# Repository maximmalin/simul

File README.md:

# FULLY AUTOMATED HARDWARE DEVELOPMENT PIPELINE.

lAST TESTED PROJECT IS DEVELOPMENT OF 2 WATT LED DRIVER 
---

**Start here**

* [`AGENT_MAP.md`](AGENT_MAP.md) — comprehensive functional map of the project (architecture, subsystems, data flow, entry points, how to run/verify).
* [`sim/COSIM_STATUS.md`](sim/COSIM_STATUS.md) — co-simulation status: what is verified, what is blocked, and why.
* [`manifest.json`](manifest.json) — machine-readable project description, generated by `python3 tools/dump_manifest.py`.
* [`technical_task_en.md`](technical_task_en.md) / [`technical_task.md`](technical_task.md) — the technical task (EN / RU).
* [`LICENSE`](LICENSE) — MIT.

---

## 1. What it is

| | |
|---|---|
| **Product** | Zero-IF (direct-conversion) SDR receiver |
| **MCU** | STM32F103C8T6 Blue Pill (Cortex-M3) |
| **Frequency range** | 0.5 – 30 MHz |
| **Architecture** | Direct conversion, quadrature I/Q, USB I/Q to host |
| **Circuit source of truth** | SKiDL (`sim/scripts/sdr_skidl_circuit.py`) — 60 parts, 38 nets |
| **Analog simulator** | ngspice 44.2 |
| **Digital/co-sim** | FMI 2.0 (`pythonfmu` / `fmpy`), QEMU (`qemu-system-arm`), PicSimLab |
| **PCB / 3D** | KiCad 9, tscircuit, FreeCAD, Elmer FEM, openEMS FDTD, NEC-2 |
| **License** | MIT |

The MCU is **never "inside" ngspice**. The analog/digital boundary is explicit at
the STM32 pins, and that contract (PA0/PA1 = ADC I/Q, PA6 = LO, PA7 = GAIN) is
asserted both by the firmware and by `verify_pin_contract.py`.

---

## 2. The spine — signal/flow of truth

```
sim/scripts/sdr_skidl_circuit.py   SKiDL = the single source of truth for connectivity
        │
        ▼
sim/scripts/export_ngspice.py      → sim/netlists/sdr_skidl_ngspice.cir (ngspice deck)
        │
        ▼
sim/scripts/build_fmu.py           → sim/fmu/SdrNgspiceFMU.fmu  (FMI 2.0 slave)
        │
        ▼
sim/scripts/cosim_fmu_stm32.py     hard-lockstep: firmware model  <->  ngspice
sim/scripts/test_fmu_cosim.py      regression through fmpy's FMI master
sim/scripts/cosim_real_stm32.py    the same, but the MCU is the real firmware.elf on QEMU
```

The system in one picture:

```
                        ┌─────────────────────────────────────────────┐
                        │            HOST / OFF-BOARD                  │
  sim/scripts/          │  SKiDL → ngspice deck → FMI FMU              │
  sdr_skidl_circuit.py  │        └── sim/netlists/sdr_skidl_ngspice.cir │
  export_ngspice.py     │                    │                         │
  build_fmu.py          │                    ▼                         │
                        │        sim/fmu/SdrNgspiceFMU.fmu             │
                        │                    │  FMI 2.0 setReal/doStep │
                        └────────────────────┼─────────────────────────┘
                                             │
             ┌───────────────────────────────┼───────────────────────────────┐
             │                               │                               │
    cosim_fmu_stm32.py           cosim_real_stm32.py            sdr_picsimlab_cosim.py
    (firmware MODEL in Python)   (REAL firmware.elf on QEMU)    (PicSimLab rcontrol)
             │                               │                               │
             │                     qemu-system-arm + GDB RSP          PicSimLab NOGUI
             │                     firmware/src/cosim.h mailbox       src/picsimlab_fmu/*
             ▼                               ▼                               ▼
      ┌──────────────────────────────── analog boundary (pins) ──────────────────┐
      │ PA0 = ADC_I   PA1 = ADC_Q   PA6 = LO (TIM3_CH1)   PA7 = GAIN             │
      └──────────────────────────────────────────────────────────────────────────┘
```

Antennas have their own physics path:

```
sim/inputs/antenna_*.yaml → sim/scripts/antenna_fdtd.py → S11/Zin
                          → sim/scripts/export_antenna_ngspice.py → Touchstone (ngspice)
```

---

## 3. Functionality index

Every piece of functionality in the repository, grouped by subsystem.

### 3.1 Circuit source of truth — SKiDL
* **`sim/scripts/sdr_skidl_circuit.py`** — the unified SKiDL netlist generator. The
  *only* place connectivity is defined: 60 parts, 38 nets. Writes the KiCad
  schematic and the netlist consumed downstream. Never hand-edit generated
  netlists; change this file and regenerate.

### 3.2 Analog netlist & ngspice
* **`sim/scripts/export_ngspice.py`** — emits the behavioral zero-IF receiver
  chain to `sim/netlists/sdr_skidl_ngspice.cir`:
  * LNA stages as transconductance macromodels (not ideal VCVS),
  * quadrature LO derived from a real 90° all-pass (`H = 1 − 2/(1+sRC)`),
  * zero-IF mixer with mid-rail-biased limiting baseband buffers,
  * RF chokes as L+R (the ferrite bead uses its DC resistance),
  * the STM32 pin boundary (see §3.4).
* Other decks: `sim/netlists/sdr_receiver.cir`, `sim/netlists/sdr_simplified.cir`,
  `sim/netlists/bridge_check.cir`.
* XSPICE bridges: analog→digital (`adc_bridge`) with datasheet CMOS thresholds;
  digital→analog modelled explicitly as a host-alterable source behind the pin's
  output resistance and load capacitance (an ngspice `dac_bridge` input cannot be
  driven from outside ngspice).

### 3.3 Direct-conversion physics (verified)
* LO is a **real 7.2 MHz timer waveform**; the beat lands at **48.1 kHz** with a
  50 kHz IF offset.
* I/Q amplitude ratio **0.965**, phase **+91.6°**.
* The **Q channel is driven by a real 90° all-pass on the LO**, not wired to zero.
* Five original analog defects (dead Q, DC LO, 0 V-centred ADC, DC-biased LNA gain,
  bare-resistor chokes) were found and fixed; the fix log lives in
  `sim/COSIM_STATUS.md`.
* Two measurement traps (ngspice `print` 80-column truncation and non-uniform
  adaptive timesteps) are documented there too.

### 3.4 STM32 pin model — datasheet-derived boundary
| Parameter | Value | Source |
|---|---|---|
| Output impedance | 65 Ω | DS5319 Table 30, I<sub>IO</sub> = 20 mA |
| Pin capacitance C<sub>IO</sub> | 5 pF | DS5319 Table 29 |
| Input low V<sub>IL</sub> | 0.35·V<sub>DD</sub> = 1.155 V | DS5319 Table 29 |
| Input high V<sub>IH</sub> | 0.65·V<sub>DD</sub> = 2.145 V | DS5319 Table 29 |
| Input leakage | 1 µA | DS5319 Table 29 |

Numbers are taken from the datasheet, not chosen for convenience.

### 3.5 Verification suite
| Script | What it proves |
|---|---|
| `sim/scripts/test_sdr_netlist.py` | 22 regression checks on the SKiDL→ngspice export |
| `sim/scripts/verify_pin_contract.py` | 31 closed-loop analog + pin-contract checks |
| `sim/scripts/test_ngspice_nets.py` | Smoke tests for the ngspice decks |
| `sim/scripts/test_fmu_cosim.py` | Drives the FMU through fmpy's FMI master, checks the pin boundary |
| `tests/requirements/**` | Requirement-matrix tests (RF, antenna, AO, system) |
| `tests/stress/test_co_simulation.py` | Bragg FMU + ngspice antenna 2-port stress test |

### 3.6 FMI 2.0 co-simulation (the FMU)
* **`sim/scripts/sdr_ngspice_fmu.py`** — a self-contained FMI 2.0 co-simulation
  slave bundling an embedded ngspice deck (self-contained on purpose: `pythonfmu`
  bundles only this one file).
* **`sim/scripts/build_fmu.py`** — regenerates the netlist from SKiDL and splices
  it into the FMU source, so the FMU and the deck are the same circuit *by
  construction*.
* **`sim/fmu/SdrNgspiceFMU.fmu`** — the built slave.
* **`sim/scripts/cosim_fmu_stm32.py`** — hard-lockstep driver: STM32 firmware
  *model* ↔ ngspice FMU. Real FMI calls (`setReal`/`doStep`/`getReal`) every step;
  pulses cross the boundary at half an LO period; PA6 drives the mixer through the
  65 Ω + 5 pF pin model.
* Build: `<venv>/bin/pythonfmu build -f sim/scripts/sdr_ngspice_fmu.py -d sim/fmu`
  (or `python3 sim/scripts/build_fmu.py`).

### 3.7 Real-firmware co-simulation on QEMU
The actual `firmware.elf` on an emulated Cortex-M, in lockstep with real ngspice.
* **`sim/scripts/cosim_real_stm32.py`** — orchestrator.
* **`sim/scripts/gdb_remote.py`** — a minimal GDB remote-serial-protocol client
  (QEMU's human monitor can read memory with `xp` but has **no write command**;
  the GDB stub can read *and* write *and* single-step).
* **`firmware/src/cosim.h`** — the RAM **mailbox** both sides agree on (magic,
  `host_lo`/`host_gain` in; `mcu_stamp`/`adc_i`/`adc_q`/`adc_stamp` out).
* **`sim/scripts/build_cosim_firmware.py`** — builds the `COSIM_MODE` ELF.
* **`sim/scripts/diag_*.py`** — forensic diagnostics that found the two setup()
  blockers (USB CDC enumeration, PLL wait) and the current stop point.

Status: the core reaches `ADC1_2_IRQHandler`; QEMU's STM32F103 peripheral model
starves `loop()` (an ADC/DMA emulator-fidelity limit). Everything around it —
mailbox, exchange, netlist, FMU — is verified. See `sim/COSIM_STATUS.md`.

### 3.8 PicSimLab bridge package (`src/picsimlab_fmu/`)
* `wrapper.py` — `PicSimLabFMU` co-simulation wrapper (`step()` / `run()`).
* `cosim_bridge.py` — TCP rcontrol ↔ ngspice lockstep loop (+ `parse_pinsl`, `MAX_SAMPLES`).
* `ngspice_bridge.py` — prompt-synced ngspice CLI pipe (`-p`) bridge.
* `pin_mapper.py` — board pin allocation (`ARDUINO_UNO`, `STM32_BLUE_PILL`, `ESP32_DEVKITC`).
* `live_scope.py` — live co-sim oscilloscope (POSIX SHM + semaphores + matplotlib).
* `examples/` — small usage examples.

Drivers and probe scripts:
* `sim/scripts/start_picsimlab.py` — launches PicSimLab NOGUI and polls until the
  rcontrol port accepts (the board comes from the `.ini`; there is **no `board`
  command** in rcontrol).
* `sim/scripts/sdr_picsimlab_cosim.py` — the SDR-specific driver.
* `sim/scripts/rcontrol.py`, `rcontrol_analog.py`, `rcontrol_session.py` —
  low-level rcontrol probing / analog pin driving / one-shot evidence session.
* Config: `firmware/picsimlab_sdr.ini`.

Blocked upstream: with the QEMU backend running, rcontrol never binds (0.9.2);
0.9.3 has rcontrol but ships no `libqemu-stm32.so`. Full evidence in
`sim/COSIM_STATUS.md`.

### 3.9 Firmware (`firmware/`)
* **`firmware/src/firmware.ino`** — minimal firmware that reaches `loop()` and
  services the mailbox.
  * Pins: `PA0` = ADC_I, `PA1` = ADC_Q, `PA6` = LO (TIM3_CH1), `PA7` = GAIN.
  * Under `COSIM_MODE`, overrides `SystemClock_Config()` to skip the PLL wait
    (QEMU never sets `PLLRDY`).
* **`firmware/src/cosim.h`** — mailbox layout shared with the co-sim host.
* **`firmware/platformio.ini`** — two environments:
  * `bluepill_f103c8` — the shipped image (USB CDC on);
  * `cosim` — USB compiled out (a bench image and a co-sim image can never be
    confused).
* **`firmware/scripts/hex.py`** — post-build `objcopy` to emit Intel HEX for
  PicSimLab's `loadhex`.

### 3.10 Antenna physics
* **`sim/inputs/antenna_*.yaml`** — one file per antenna; adding an antenna = add
  a YAML file, no code edits. Present: dipole 7 MHz, meander 200 MHz, patch
  2.45 GHz.
* **`sim/scripts/antenna_fdtd.py`** — YAML → S11/Zη → Touchstone. All three
  shipped antennas run the **real openEMS FDTD** solver (`fdtd: true`); setting
  `fdtd: false` falls back to an analytic thin-wire / transmission-line estimate
  (marked `model: analytic` in the JSON).
* **`sim/scripts/mesh.py`** — openEMS mesh sizing with a hard memory budget.
* **`sim/scripts/export_antenna_ngspice.py`** — results → ngspice S-parameter networks.
* **`sim/scripts/antenna_sim.py`**, **`smoke_tutorial.py`** — openEMS workflow and
  tutorial smoke test.
* **`sim/scripts/radiation.py`**, **`sim/nec/**`** — NEC-2 radiation patterns for
  the three channels (`sim/nec/channel_{a,b,c}.nec`, `run_nec.py`).
* **`hardware/antenna/**`** — FreeCAD panel geometry (150 × 150 mm FR-4 0.8 mm):
  * Channel A: meander 200 MHz, Channel B: 2×2 patch @ 2.45 GHz, Channel C: 4×4
    patch @ 5.8 GHz; `geometry/build_antennas_fc.py` rebuilds and exports
    STEP/STL.
* Results (`sim/outputs/*.json`, all `model: fdtd`):
  * dipole 7 MHz — f<sub>res</sub> 6.90 MHz, S11 −15.7 dB, η<sub>rad</sub> 98 %.
  * patch 2.45 GHz — f<sub>res</sub> 2442.5 MHz, S11 ≈ −3.6 dB, η<sub>rad</sub> 30.8 %.
  * meander 200 MHz — no usable match anywhere in 50–800 MHz: S11 ≈ 0 dB and
    Z<sub>in</sub> ≈ 5 − 63j Ω at 50 MHz, with |Re Z| only ≈ 0.6–2 Ω at the in-band
    reactance zeros. The printed meander over its full ground plane is a low-Q,
    low-resistance resonator, so the old analytic −12.0 dB estimate was
    optimistic; the FDTD reports the element as effectively non-radiating
    (η = 0 %, `eta_source: unavailable_no_radiated_power`). A genuine full-wave
    result, not a solver failure.

### 3.11 Web GUI
* **`sim/web_gui/app.py`** — Flask app that runs `SdrNgspiceFMU.fmu` via `fmpy`,
  plots I/Q live, exposes `stim_level` / `lo_frequency`, and exports an
  `sdr_cosim.xcos` diagram for Xcos.
* **`sim/web_gui/templates/index.html`** — Plotly dark dashboard.
* Run: `python3 sim/web_gui/app.py` → http://localhost:5000.

### 3.12 Diagnostics
`sim/scripts/diag_*.py` (`infinite`, `literal`, `mailbox`, `pc`, `regs`, `watch`,
`patch`) are the forensic scripts used to find the QEMU blockers and validate the
patch antenna. Kept as the reproducible evidence trail, not scratch.

### 3.13 Hardware / PCB / 3D toolchain
* **`hardware/tscircuit/build_pcb.mjs`** — the PCB stage. Reads the SKiDL netlist
  (`sim/scripts/sdr_skidl_circuit.py` → `hardware/kicad/sdr_receiver.kicad_sch`),
  places parts, autoroutes with explicit Altium-grade design rules and exports
  `out/`: `board.kicad_pcb`, `board.kicad_sch`, `gerbers.zip`, `board.step`,
  `board.{glb,gltf}`, `board.net`, `board_schematic.pdf`, `circuit.json`.
  Run `node hardware/tscircuit/build_pcb.mjs` (or `make pcb`).
* The earlier `hardware/kicad/build_board.py` (`kinet2pcb` + `kicad-cli`) path is
  superseded by the tscircuit emitter.
* **Reliability** — `sim/octave/reliability_model.m` (Octave) reads datasheet
  parameters from `sim/octave/reliability_parts.tsv` (base FIT, Ea, T_ref/T_use,
  π_Q) and computes system MTBF as parts-count + Arrhenius. Requirement **REQ-REL-01**
  (MTBF ≥ 10 000 ч). Run `make reliability` → `out/reliability.json`;
  tests in `tests/requirements/reliability/`.
* **Thermal** — `sim/scripts/thermal_pcb.py` couples **ngspice** (DC operating
  point → dissipated power) with the **PCB CAD** (`circuit.json` → outline,
  stackup, placement). Two levels: *fast* `T_j = T_a + P·θ_JA` and a *deep* 2D FEM
  of heat conduction/spreading over the board. Run `make thermal` →
  `out/thermal_{fast,fem}.json`; tests in `tests/requirements/thermal/`.
* **Reception distance (link budget)** — `sim/scripts/link_budget.py` computes the
  receiver noise floor (REQ-PERF-02), MDS (REQ-PERF-02) and the Friis range per antenna
  channel (A/B/C). Run `make link-budget` → `out/link_budget.{json,svg}`;
  «дальность приёма» сводится по разделам в `requirements/reception_range.md`
  (и столбец `Reception_Distance_m` в `requirements_matrix.csv`).
* **Direction finding** — `sim/scripts/direction_finding.py` implements a phase
  interferometer (Δφ = 2π·d·sinθ/λ), draws the combined bearing + range diagram,
  and emits a NEC-2 `.nec` that opens in
  [EA1FUO/AntennaSim](https://github.com/EA1FUO/AntennaSim)
  (`--antennasim-url` posts to its `/api/v1/simulate`). Run `make direction` →
  `out/direction_finding.{json,svg}`.
* **EMC** — `tests/requirements/emc/` verifies REQ-EMC-01…04: skin depth and
  shielding effectiveness, immunity to 3 V/m (IEC 61000-4-3 level 2), CISPR 22
  Class B emission, supply filters and enclosure zoning.
* `tools/spec.py`, `tools/blocks.py` — the project spec (6 blocks, 24 parts) used
  by the generators.
* `hardware/pipeline.py` — hardware build-pipeline orchestrator.
* `hardware/kicad/kicad_lib.py` — KiCad symbol / schematic helper;
  `hardware/kicad/generate_schematic.py` — full single-sheet `.kicad_sch`
  generation from code; `test_any_schematic.py` — prove the generator is
  schematic-agnostic; `verify_nets.py` — cross-check the KiCad netlist against the
  generator tables.
* `hardware/tscircuit/build_pcb.mjs` — netlist → TSX, placement, model offsets;
  `build_derived.py` (build local derived tables from the JLCPCB part DB),
  `resolve_parts.py` (part substitution by value/footprint), `step2stl.py`
  (STEP → STL with orientation normalization), `check_models3d.py` (glb vs
  circuit.json), `make_viewer.py` + `site_assets.py` (offline 3D viewer),
  `fetch_vendor_models.mjs` / `fetch_3dmodels*.sh` (vendor 3D models),
  `check_net.py` (verify the viewer makes no external requests).
* Part selection / datasheets: `scripts/download-datasheets.js`,
  `scripts/convert-kicad-to-circuit-json.js`, `scripts/post-build-datasheets.js`,
  `scripts/lib/*`.
* Manufacturing output dir: `out/` (board.kicad_pcb, gerbers, BOM, PnP, GLB, STEP).

### 3.14 Engineering drawings & power budget
* **`gost_pipeline.py`** — STEP → cleaned → GOST drawing.
* **`block0_bus_power_calc.py`** — 5 V bus / buck / LC-filter calculation.
* **`gen_spice_from_kicad.py`** — KiCad `.kicad_sch` → SPICE netlist.
* `picsimlab_rt_wrapper.py` — PicSimLab real-time wrapper (from brig-receiver).

### 3.15 Bragg-cell / AOPP toolbox (transferred from brig-receiver)
The acousto-optic branch is kept as a toolbox, **not** part of the SDR signal path:
* **`sim/scripts/bragg_sim.py`** — Gmsh → Elmer FEM pipeline (`Δn = dn_scale·ε_zz`).
* **`sim/scripts/bragg_fmu.py`**, `test_fmu.py`, `test_antenna_fmu.py`,
  `realtime_loop_fmu.py` — FMI blocks and real-time FMU loop.
* **`sim/scripts/msh_to_elmer.py`** — Gmsh `.msh` → Elmer mesh.
* **`sim/inputs/bragg_inputs.yaml`**, `config/params.yaml` — parameters.
* **`sim/octave/bragg_formulas.m`** + `README_formulas.md` — formulas and an
  analytic self-check (Hooke + photoelasticity).
* **`sim/cad/`** — FreeCAD parametric Bragg-cell scripts: `make_bragg_cell_fc.py`
  (build), `refresh_cad.py` (regenerate), `import_elmer_mesh_fc.py`, `cad_dims.json`.
  No `.FCStd`/`.step` is checked in — they are generated.
* `sim/outputs/elmer_results.json`, `sim/outputs/nec_results.json`, `openems_results.json`.

### 3.16 Requirements, plan, tests & CI
* **Requirements matrix** — `requirements/requirements_matrix.csv` (37 requirements + header) and
  per-subsystem `requirements/*/REQ-*.md`; SNR and noise floor are project-wide
  requirements **REQ-PERF-02** (SNR, noise floor, MDS).
* **Plan** — `plan/plan.md`, `plan/blocks.md`, `plan/README.md`, `plan/checks.py`.
* **Technical task** — `technical_task.md` (RU), `technical_task_en.md` (EN),
  `technical_task_ua.md` (UA), plus per-block TZ in `work/tz-{a..e}/`.
* **Tests** — pytest suites under `tests/requirements/{antenna,rf,ao,system,reliability,thermal}/`,
  `tests/stress/test_co_simulation.py` (co-simulation, needs `fmpy`);
  checklist at `tests/requirements/checklist.csv`.
* **CI** — `.forgejo/workflows/push-{general,fix,feature,docs}.yml` (Elmer-FEM
  physical-constraint jobs on push).
* `references/formulas_and_sources.md`, `issues/` (issue template folder).

### 3.17 Tooling
* **`tools/dump_manifest.py`** — writes `manifest.json`.
* **`tools/init_project.py`** — create a fresh project from tracked files.

---

## 4. Quick start

```bash
cd <repo>

# --- Everything (netlist → PCB → docs → tests → reliability/thermal) ---
make all

# --- Circuit → netlist ---
.venv/bin/python sim/scripts/sdr_skidl_circuit.py     # regenerate SKiDL netlist
.venv/bin/python sim/scripts/export_ngspice.py        # regenerate ngspice deck

# --- Verify (fastest health check) ---
.venv/bin/python sim/scripts/test_sdr_netlist.py      # 22/22 checks
.venv/bin/python sim/scripts/verify_pin_contract.py   # 31/31 checks
.venv/bin/python sim/scripts/test_ngspice_nets.py

# --- FMU co-simulation ---
python3 sim/scripts/build_fmu.py                      # rebuild FMU from SKiDL
.venv/bin/python sim/scripts/cosim_fmu_stm32.py       # lockstep firmware-model ↔ ngspice
.venv/bin/python sim/scripts/test_fmu_cosim.py        # fmpy regression

# --- Real firmware on QEMU ---
.venv/bin/python sim/scripts/build_cosim_firmware.py  # COSIM_MODE ELF
.venv/bin/python sim/scripts/cosim_real_stm32.py      # real firmware ↔ ngspice

# --- PicSimLab ---
.venv/bin/python sim/scripts/start_picsimlab.py       # launch NOGUI, wait for rcontrol
.venv/bin/python sim/scripts/sdr_picsimlab_cosim.py   # drive co-sim

# --- Antennas ---
export LD_LIBRARY_PATH=$HOME/opt/openEMS/lib:$LD_LIBRARY_PATH
<venv-with-openEMS>/bin/python sim/scripts/antenna_fdtd.py sim/inputs/antenna_patch_2450mhz.yaml
.venv/bin/python sim/scripts/export_antenna_ngspice.py sim/outputs/<result>.json

# --- Firmware build ---
cd firmware && pio run                # shipped image
cd firmware && pio run -e cosim       # USB-less co-sim image
cd firmware && pio run -t hex         # emit Intel HEX

# --- Web GUI ---
python3 sim/web_gui/app.py            # http://localhost:5000

# --- Hardware / manifest ---
node hardware/tscircuit/build_pcb.mjs         # real tscircuit emitter
python3 hardware/tscircuit/build_derived.py   # local part table
python3 hardware/tscircuit/resolve_parts.py   # part substitution
python3 tools/dump_manifest.py                # write manifest.json
node scripts/download-datasheets.js           # fetch MPN datasheets
python3 gost_pipeline.py                       # STEP → cleaned → GOST drawing

# --- Reliability / thermal ---
make reliability                              # Octave parts-count MTBF (REQ-REL-01)
make thermal                                  # fast θ_JA + 2D FEM (PCB CAD + ngspice)

# --- Reception distance / direction finding / EMC ---
make link-budget                              # Friis + шум → out/link_budget.{json,svg}
make direction                                # пеленгация (NEC-2 / AntennaSim)
pytest tests/requirements/emc tests/requirements/reception -q
```

> `.venv/bin/python` is the project venv (`skidl`, `pythonfmu`, `fmpy`, `numpy`,
> `matplotlib`). Pure-stdlib tools run fine under system `python3`; the web GUI
> uses `flask` (system `python3`), and antenna FDTD needs a separate
> openEMS-enabled interpreter.

---

## 5. Repository layout

Roles: **source** = keep and edit; **derived** = regenerated by scripts; **data** =
external/binary.

| Path | Role | What it is |
|---|---|---|
| `sim/scripts/` | source | All physics, netlist, co-sim, antenna, diagnostic scripts |
| `sim/netlists/` | derived | ngspice decks (`.cir`) produced by `export_ngspice.py` |
| `sim/inputs/` | source | YAML parameter files (one per antenna) |
| `sim/outputs/` | derived | Physics result JSON/PNG |
| `sim/fmu/` | data | Built FMUs (`SdrNgspiceFMU.fmu`, antenna/Bragg blocks) |
| `sim/work/` | derived | Solver scratch (openEMS, Elmer, gmsh) |
| `sim/web_gui/` | source | Flask I/Q web GUI for the FMU |
| `firmware/` | source | STM32 Arduino sketch, cosim mailbox, PlatformIO config |
| `firmware/src/` | source | `firmware.ino`, `cosim.h` |
| `src/picsimlab_fmu/` | source | PicSimLab rcontrol ↔ ngspice bridge package |
| `hardware/` | source | KiCad generation, PCB/3D pipeline, antenna geometry, FEM |
| `hardware/kicad/` | source | Schematic generator + KiCad symbol/S-expression library |
| `hardware/tscircuit/` | source | PCB emitter, 3D model resolution, part selection, viewer |
| `tools/` | source | Spec (`spec.py`, `blocks.py`), manifest/init tooling |
| `tests/` | source | Requirement-matrix + stress tests |
| `requirements/`, `plan/`, `work/`, `tz/`, `references/`, `config/`, `issues/` | source | Requirements, plan, TZ, formulas, parameters |
| `local_footprints/` | external | Опциональный клон [KiCad/kicad-footprints](https://github.com/KiCad/kicad-footprints) для ручной правки плат в KiCad. Не входит в репозиторий и не нужен для сборки: плату генерирует tscircuit, футпринты берутся из resolved-таблицы деталей. |
| `out/` | derived | Generated board artifacts (gerbers/BOM/GLB/STEP) |
| `node_modules/`, `.venv/` | derived | Dependency installs |
| `.forgejo/` | source | CI workflow definitions |
| `scripts/` | source | Node datasheet/part-selection helpers |

---

## 6. Environment

**System tools:** `python3` (3.13), `ngspice` (44.2), `kicad-cli` (9.0.2),
`node`/`npm` (22 / 10), `pio` (PlatformIO 6.2), `qemu-system-arm` (10.0),
`gdb-multiarch` (16.3), `gmsh` (4.13), Elmer FEM (26.2), openEMS, NEC-2
(`nec2c`), FreeCAD.

**Python venv (`.venv`):** `skidl` 2.3.0, `pythonfmu` 0.7.0, `fmpy` 0.3.32,
`numpy` 2.5.3, `matplotlib`. `flask` is *not* installed here — the web GUI runs
under system `python3` (flask 3.1); `pytest` is installed separately for the
`tests/` suites. Antenna FDTD needs a *separate* openEMS-enabled interpreter.

**External data / installs:**
* `/usr/share/kicad/{symbols,footprints}`
* `$HOME/opt/openEMS` — openEMS install (used via `LD_LIBRARY_PATH`)
* `/mnt/ext4data/jlcparts` — JLCPCB parts DB used by the part resolver
* Elmer / gmsh for the FEM path

**PicSimLab:** NOGUI AppImages in `/mnt/ext4data/downloads/`
(`PICSimLab_NOGUI-0.9.2` has the STM32 backend; `0.9.3` has a working rcontrol but
ships no `libqemu-stm32.so`). See `sim/COSIM_STATUS.md`.

---

## 7. Verified status

| Stage | Evidence |
|---|---|
| SKiDL netlist | 60 parts, 38 nets, KiCad schematic written |
| ngspice deck | `sim/netlists/sdr_skidl_ngspice.cir`, 0 warnings / 0 errors |
| Direct conversion | LO is a real 7.2 MHz timer waveform; beat lands at 48.1 kHz (IF offset 50 kHz); I/Q ratio 0.965; phase +91.6° |
| Q channel | driven by a real 90° all-pass on the LO, not wired to zero |
| STM32 pin model | 65 Ω @ 20 mA; C<sub>io</sub> 5 pF; V<sub>IL</sub>/V<sub>IH</sub> 0.35/0.65·V<sub>DD</sub> |
| Regression tests | `test_sdr_netlist.py` — 22/22 |
| Analog + pin contract | `verify_pin_contract.py` — 31/31 |
| Firmware | cosim build artifacts present (`firmware/.pio/build/cosim/`): `firmware.elf` ≈ 23 KB, `firmware.bin` ≈ 4.6 KB; `.hex` via `pio run -t hex` |
| Antennas | all real openEMS FDTD (`model: fdtd`): dipole 6.90 MHz / S11 −15.7 dB / η<sub>rad</sub> 98 %; patch 2442.5 MHz / −3.6 dB / 31 %; meander reactive with no in-band match (S11 ≈ 0 dB, η<sub>rad</sub> 0 %) — `sim/outputs/*.json` |
| PicSimLab NOGUI rcontrol | answers `version`, `pinsl`, `sim`, `loadhex` |
| STM32 backend | `qemu-stm32 -M stm32-f103c8-picsimlab-new`, 48 pins |

---

## 8. Known limitations / open items

1. **QEMU real-firmware path** stops at `ADC1_2_IRQHandler` — QEMU's STM32F103
   ADC/DMA model is not faithful enough for `loop()` to be serviced. Emulator
   fidelity limit, not a project defect.
2. **PicSimLab rcontrol never binds while QEMU runs** (0.9.2), and **0.9.3 has no
   STM32 backend**. Needs an upstream fix / a 0.9.3-built `libqemu-stm32.so`.
3. **`out/` artifacts are text templates**, not manufacturing outputs.
4. Several transferred brig scripts assume brig's paths/data (e.g. `config/params.yaml`
   points at `/home/mirrage/brig-receiver/...`); adapt before use. Likewise
   `sim/README.md` is the brig Bragg-cell module README, kept as reference.
6. `docs/` is empty; `AGENT_MAP.md` + `sim/COSIM_STATUS.md` + `manifest.json` are
   the authoritative documentation.
7. **Meander 200 MHz does not match in full-wave simulation.** Modelled over its
   full ground plane (matching `hardware/antenna/geometry/build_antennas_fc.py`)
   it is a low-Q reactive resonator — S11 ≈ 0 dB across 50–800 MHz, no net
   radiation (η = 0 %). The project's own definitions also disagree: the YAML/CAD
   use 3 × 63.5 mm arms (220 mm), while `sim/nec/run_nec.py` uses 3 × 130 mm arms
   (430 mm) and its `GN 1 0 0 0 1.0 0.0` ground card is rejected by nec2c. Treat
   the meander figures as a design warning, not a finished antenna.

---

## 9. Conventions

* **One source of truth per thing.** Connectivity = SKiDL; physics = the
  `sim/scripts/*` entry points; parameters = YAML in `sim/inputs/`.
* **Don't hand-edit derived files** (`sim/netlists/`, `sim/outputs/`, `out/`).
* **Pin boundary is a contract.** PA0/PA1 = ADC I/Q, PA6 = LO, PA7 = GAIN. Asserted
  by `verify_pin_contract.py` and by `firmware.ino`.
* **Datasheet numbers, not convenience.** Pin impedance and thresholds come from
  DS5319.
* **Prove it.** Any claim about the analog chain should be backed by
  `test_sdr_netlist.py` / `verify_pin_contract.py` / `test_fmu_cosim.py`.
* **Regenerate, don't patch.** `build_fmu.py` exists precisely so the FMU can't
  drift from SKiDL.

See [`AGENT_MAP.md`](AGENT_MAP.md) for the deep functional map and
[`sim/COSIM_STATUS.md`](sim/COSIM_STATUS.md) for the co-simulation narrative and
evidence.

## 🤖 Агентно-функциональный граф

Заказ приходит текстом, проходит граф функций-агентов и превращается
в сборку. Движок **не знает про Krystal Radio** — всё, что касается
конкретного изделия, лежит в [`agents.project.yaml`](agents.project.yaml).

```
POST /api/order "посчитай дальность и пеленгацию"
        │
        ▼
   ┌──────────┐  модель получает инструменты и решает:
   │supervisor│  list_targets → submit_plan → run_target → read_artifacts
   └────┬─────┘  (или ask_human, когда нужен человек)
        ▼
   ┌──────┐  выполняет вызовы, возвращает модели результат
   │ tools│
   └──┬───┘
      ├─ нужна помощь ─► await_human ─► interrupt() ─► ответ оператора ─┐
      ├─ есть модель ──► supervisor (цикл: думаю → действую → смотрю)  │
      └─ нет модели ───► plan_rules → execute_rules → review          │
                                                                        │
   ┌────────┐ ◄───────────────────────────────────────────────────────┘
   │ report │  факты из артефактов → структурный отчёт (+ резюме модели)
   └────────┘
```

### Почему LangGraph, а не что-то другое

Проверено по документации LangChain: **LangGraph — это agent runtime,
LangChain — framework, Deep Agents — harness**. Runtime даёт наибольший
контроль над тем, что именно выполняется.

Здесь контроль — главное требование. Модель **выбирает** из объявленных
целей, а **исполняет** система сборки. Harness вроде CrewAI или Deep
Agents даёт ReAct-агента с доступом к файловой системе — то есть
ровно то, чего в инженерном проекте быть не должно: агент с правом
писать что угодно был бы не помощью, а источником порчи.

Что взято из рантайма по-современному:

| Возможность | Как реализовано |
|---|---|
| Вызов инструментов | Типизированные схемы в `backend/agents/tools.py`, ответ приходит разобранным. Прежний разбор JSON регуляркой не нужен |
| Цикл «думаю — действую — смотрю» | Узлы `supervisor` ↔ `tools`, не один план на всё |
| Прерывание человека | `interrupt()` — граф встаёт, состояние сохранено, после ответа продолжается с места остановки |
| Долговременное состояние | `SqliteSaver` в `.run/graph.db`; переживает перезапуск моста |
| Устойчивость к обрыву | Недоступный провайдер уходит в паузу на `KR_LLM_COOLDOWN` секунд, чтобы не ждать таймаут на каждом вызове |

Без `langgraph` движок работает на запасном пути (`run_plain`): те же
узлы, те же проверки — теряются только чекпоинты и прерывание.

### Модели: свободные веса, любой рантайм

`Authorization` не отправляется, если ключа нет — поэтому один и тот же
код работает и с облаком, и с локальным сервером. Локальные серверы
**находятся сами**: опрашиваются типовые порты (`11434`, `8080`,
`1234`, `8000`, `5000`…), так что не важно, запущен Ollama, llama.cpp,
LM Studio или vLLM.

```bash
make llm-check                            # что включено, что отвечает, какие модели есть
KR_LLM_PRESET=hermes make llm-check       # то же для другой открытой модели
KR_LLM_ENABLED=0 make llm-check           # проверить, что будет при выключенной модели
```

| Переменная | Смысл |
|---|---|
| `KR_LLM_ENABLED` | Главный выключатель. `0` — план по правилам, сводки структурные |
| `KR_LLM_PRESET` | `hermes`, `qwen`, `llama`, `gemma`, `mistral` |
| `KR_LLM_PROVIDER` | `ollama`, `llamacpp`, `lmstudio`, `vllm`, `openai`, `deepseek`, `groq`, `custom` |
| `KR_LLM_MODEL` | Модель. Если её нет на сервере — подставится та, что есть |
| `KR_LLM_MODEL_FAST` | Отдельная модель для сводок (обычно локальная и дешёвая) |
| `KR_LLM_FALLBACK` | `auto` — откат на живой локальный сервер, либо имя провайдера |

Роли разделены намеренно: планирование требует аккуратного разбора
формулировки, сводка — нет. Сводить второе на слабую локальную модель
безопасно, потому что **модель не выдумывает числа**: она читает их
из артефактов (`backend/agents/reporter.py`).

> Про эту машину: 8 ядер, 11 ГБ RAM, GPU нет. Hermes 3 Llama 3.1 8B
> (4.9 ГБ) здесь даёт единицы токенов в секунду — для агентного цикла
> непригодно. Практичен `qwen2.5:3b-instruct`; Hermes имеет смысл
> включать на машине с видеокартой.

### Никакой конкретики в движке

Это проверяется тестом, а не обещанием: `tests/requirements/agents`
создаёт посторонние проекты (make, npm, just, пустой) и требует, чтобы
движок с ними работал. Отдельный тест разбирает AST движка и падает,
если в коде появятся имена целей или файлы артефактов этого проекта.

### OpenCode на тех же бесплатных моделях

OpenCode умеет любой OpenAI-совместимый провайдер, поэтому работает на
том же ключе и тех же моделях, что и наш движок:

```bash
./scripts/oc.py --write     # обновить opencode.json
./scripts/oc.py             # обновить и запустить
./scripts/oc.py run "собери всё и проверь тестами"
```

`scripts/oc.py` не зашивает список моделей и не доверяет каталогу:

* спрашивает `/v1/models`, оставляет помеченные `:free`;
* **проверяет каждую живым запросом.** Суффикс `:free` — не гарантия:
  из семи моделей в момент проверки шесть отвечали, одна отвечала
  «This model is no longer free», несколько отдавали 429 по fair-share.
  Без проверки модель по умолчанию могла оказаться нерабочей, а ошибка
  выглядела бы как «Payment required» — будто ключ не тот;
* ключ берёт из `~/.hermes/auth.json` и кладёт в `.env` (в `.gitignore`),
  а не в конфиг: он живёт около часа, и захардкоженный завтра даст 401;
* подставляет его через `settings.apiKey`. Поле `env` управляет
  хранилищем учётных данных самого OpenCode и пакету
  openai-compatible ключа не передаёт.

Там же прописан наш MCP-сервер, поэтому связка замкнута:

```bash
opencode run "посчитай дальность и пеленгацию"
# → бесплатная модель в облаке → MCP → граф → make → артефакты
```

### Изоляция заказов

Каждый заказ выполняется в `work/orders/<id>`: исходники проекта копируются,
`.venv` и `node_modules` подключаются символическими ссылками, `out/`
создаётся свой. Проект — опора работы агентов, и заказ не имеет возможности
их переписать. Артефакты забираются наружу только при успешном выполнении.

Отключается, если песочница не нужна:

```bash
KR_SANDBOX=0 make run
```

### Команды

```bash
make agents-check                       # что движок увидел в проекте
make agents-graph                       # узлы графа
make agents-ask  TEXT="нужен водопад"   # разобрать заказ, ничего не запуская
make agents-run  TEXT="собери всё"      # выполнить заказ
make run                                # мост + интерфейс по одному адресу
```

Порядок живого прогона (что поднять, куда постить заказ, где песочница
и архив, какие env-ручки) — в [`docs/RUN_LIVE_ORDER.md`](docs/RUN_LIVE_ORDER.md).

---

## License

MIT — see [`LICENSE`](LICENSE).

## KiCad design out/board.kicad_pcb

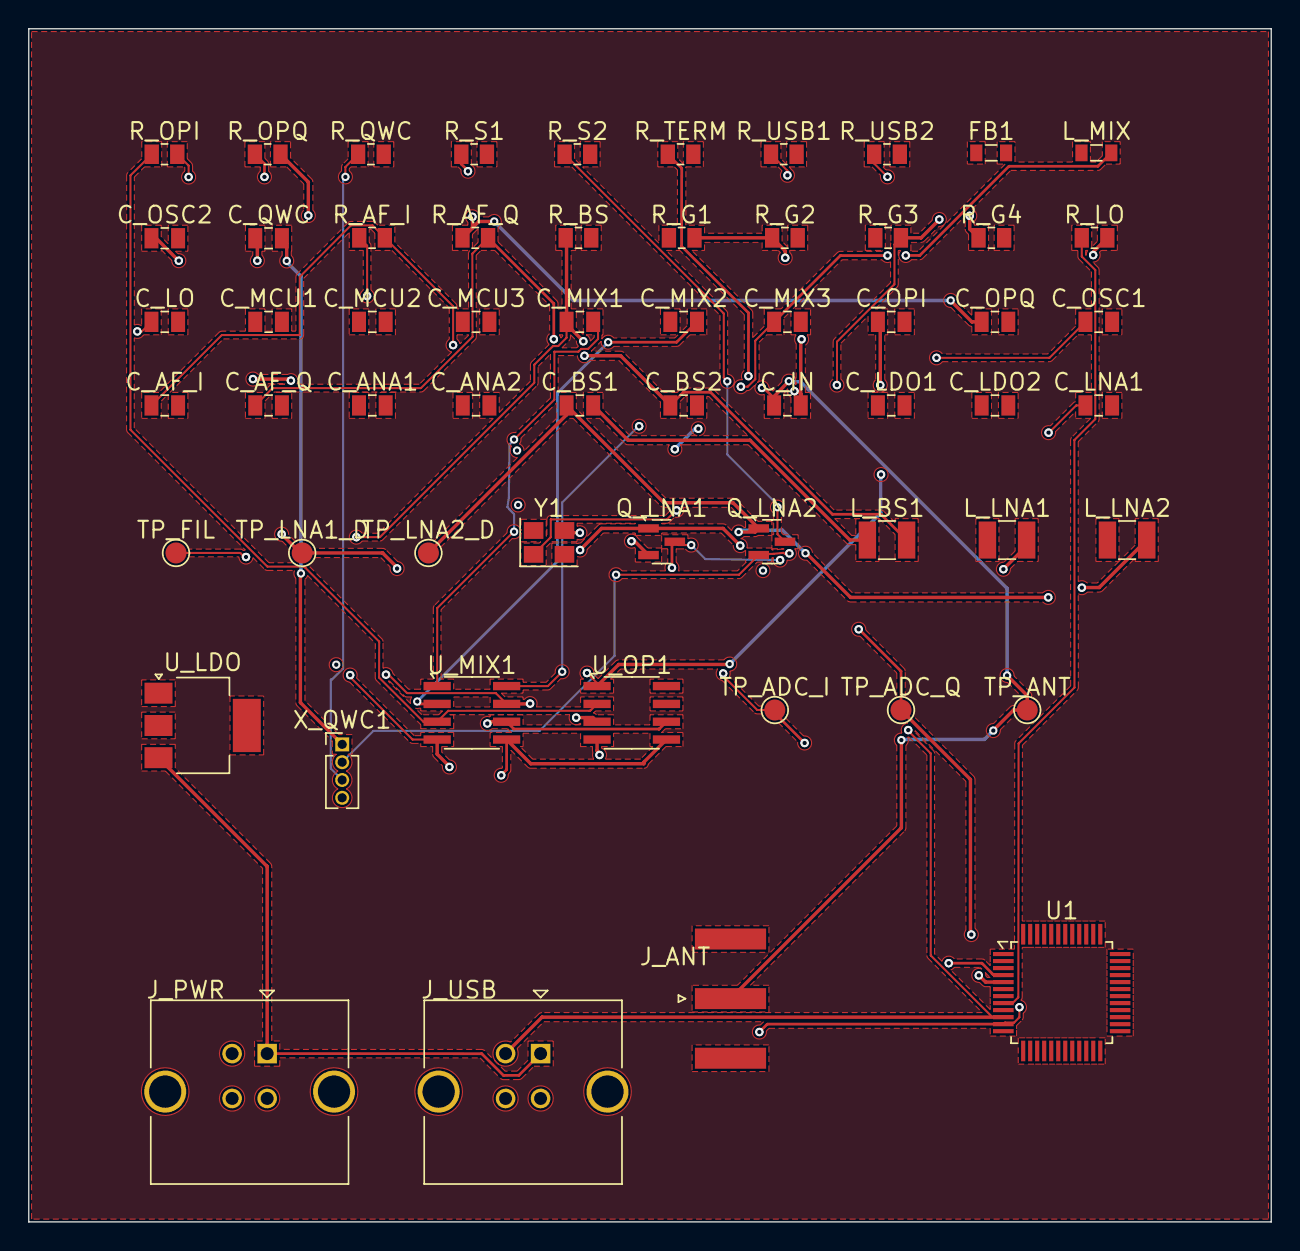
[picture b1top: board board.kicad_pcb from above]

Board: 4 copper layers, 88.6 x 85.1 mm, 60 parts (0 on the bottom side), 29 nets.

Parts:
C_AF_I: 100p
C_AF_Q: 100p
C_ANA1: 10u
C_ANA2: 100n
C_BS1: 100p
C_BS2: 10p
C_IN: 100p
C_LDO1: 100u
C_LDO2: 100n
C_LNA1: 100p
C_LO: 100p
C_MCU1, C_MCU2: 100n
C_MCU3: 4u7
C_MIX1, C_MIX2: 100p
C_MIX3: 100n
C_OPI: 100p
C_OPQ: 100p
C_OSC1, C_OSC2: 22p
C_QWC: 100p
FB1: 600R@100MHz; 600R_100MHz
J_ANT: SMA_EDGE
J_PWR: 5V_IN
J_USB: USB_CDC
L_BS1: 100u
L_LNA1, L_LNA2: 18u
L_MIX: 600R@100MHz; 600R_100MHz
Q_LNA1, Q_LNA2: 2N7002
R_AF_I: 10k
R_AF_Q: 10k
R_BS: 1k
R_G1, R_G2: 10k
R_G3: 4k7
R_G4: 2k2
R_LO: 50
R_OPI: 10k
R_OPQ: 10k
R_QWC: 1k
R_S1, R_S2: 1k
R_TERM: 50
R_USB1, R_USB2: 22
TP_ADC_I: TESTPOINT
TP_ADC_Q: TESTPOINT
TP_ANT: TESTPOINT
TP_FIL: TESTPOINT
TP_LNA1_D, TP_LNA2_D: TESTPOINT
U1: STM32F103C8T6
U_LDO: AMS1117-3.3; AMS1117-3_3
U_MIX1: LT5560
U_OP1: OPA2134
X_QWC1: LPJ-1
Y1: 8MHz

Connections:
ADC_I: C_OPI.1, R_AF_I.1, U_OP1.1
ADC_I_F: C_AF_I.1, R_AF_I.2, TP_ADC_I.1, U1.4
ADC_Q: C_OPQ.1, R_AF_Q.1, U_OP1.4
ADC_Q_F: C_AF_Q.1, R_AF_Q.2, TP_ADC_Q.1, U1.5
FIL_IN: C_BS1.2, L_BS1.1
FIL_OUT: C_BS2.1, C_MIX1.1, L_BS1.2, R_BS.1, TP_FIL.1
LNA1_D: C_QWC.1, L_LNA1.2, Q_LNA1.1, TP_LNA1_D.1
LNA1_G: C_IN.2, Q_LNA1.2, R_G1.2, R_G2.1
LNA1_S: C_LNA1.1, Q_LNA1.3, R_S1.1
LNA2_D: C_BS1.1, L_LNA2.2, Q_LNA2.1, TP_LNA2_D.1
LNA2_G: Q_LNA2.2, R_G3.2, R_G4.1, X_QWC1.2
LNA2_S: Q_LNA2.3, R_S2.1
LO: C_LO.1, R_LO.2, U_MIX1.7
LO_SRC: R_LO.1, U1.8
MIX_I1: R_OPI.1, U_MIX1.3, U_OP1.2
MIX_I2: R_OPI.2, U_MIX1.4, U_OP1.3
MIX_IN_N: C_MIX2.2, U_MIX1.2
MIX_IN_P: C_MIX1.2, U_MIX1.1
MIX_Q1: R_OPQ.1, U_MIX1.5, U_OP1.5
MIX_Q2: R_OPQ.2, U_MIX1.6, U_OP1.6
OSC_IN: C_OSC1.1, Y1.1
OSC_OUT: C_OSC2.1, Y1.3
QWC_CP: R_QWC.1, X_QWC1.3
QWC_IN: C_QWC.2, X_QWC1.1
RF_IN: C_IN.1, J_ANT.1, R_TERM.1, TP_ANT.1
USB_DP: J_USB.2, R_USB1.1, U1.10
USB_D_: J_USB.3, R_USB2.1, U1.11
VCC_MIX: C_MIX3.1, L_MIX.2, U_MIX1.8
VIN_5V: J_PWR.1, J_USB.1, U_LDO.3
